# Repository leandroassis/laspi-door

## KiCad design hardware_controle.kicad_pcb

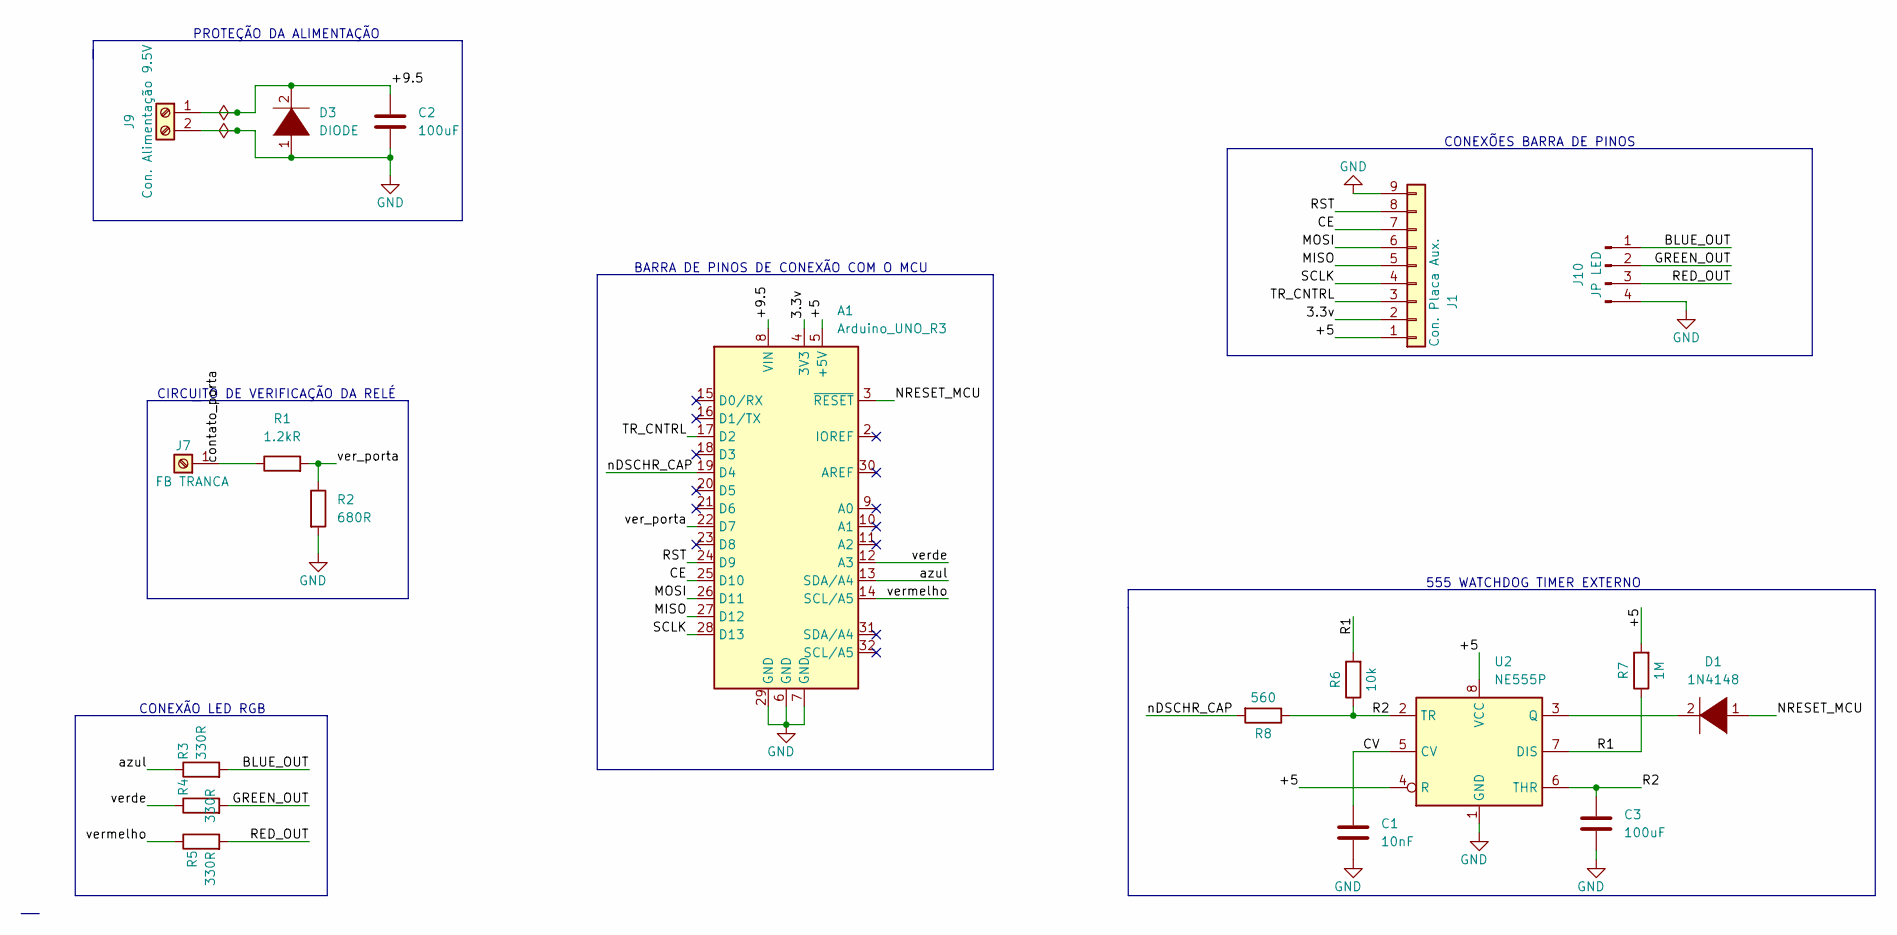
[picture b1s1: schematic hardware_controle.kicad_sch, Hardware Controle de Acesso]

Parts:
A1: Arduino_UNO_R3
C1: 10nF; C_Radial_D8.0mm_H11.5mm_P3.50mm
C2, C3: 100uF; C_Radial_D8.0mm_H11.5mm_P3.50mm
D1: 1N4148; D_DO-41_SOD81_P7.62mm_Horizontal
D3: DIODE; D_DO-41_SOD81_P7.62mm_Horizontal
J1: Con. Placa Aux.; PinHeader_1x09_P2.54mm_Vertical
J7: FB TRANCA; TerminalBlock_RND_205-00012_1x02_P5.00mm_Horizontal
J9: Con. Alimentação 9.5V; TerminalBlock_RND_205-00012_1x02_P5.00mm_Horizontal
J10: JP LED; PinHeader_1x04_P2.54mm_Vertical
R1: 1.2kR; R_Axial_DIN0207_L6.3mm_D2.5mm_P10.16mm_Horizontal
R2: 680R; R_Axial_DIN0207_L6.3mm_D2.5mm_P10.16mm_Horizontal
R3, R4, R5: 330R; R_Axial_DIN0207_L6.3mm_D2.5mm_P10.16mm_Horizontal
R6: 10k; R_Axial_DIN0207_L6.3mm_D2.5mm_P10.16mm_Horizontal
R7: 1M; R_Axial_DIN0207_L6.3mm_D2.5mm_P10.16mm_Horizontal
R8: 560; R_Axial_DIN0207_L6.3mm_D2.5mm_P10.16mm_Horizontal
U2: NE555P; DIP-8_W7.62mm

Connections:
/3.3v: A1.4 (3V3), J1.2
/+5: A1.5 (+5V), J1.1, R7.2, U2.4 (R), U2.8 (VCC)
/+9.5: A1.8 (VIN), C2.1, D3.2 (A), J9.1
/BLUE_OUT: J10.1, R3.2
/CE: A1.25 (D10), J1.7
/CV: C1.1, U2.5 (CV)
/GREEN_OUT: J10.2, R4.2
/MISO: A1.27 (D12), J1.5
/MOSI: A1.26 (D11), J1.6
/NRESET_MCU: A1.3 (~RESET), D1.1 (K)
/R1: R6.2, R7.1, U2.7 (DIS)
/R2: C3.1, R6.1, R8.1, U2.2 (TR), U2.6 (THR)
/RED_OUT: J10.3, R5.2
/RST: A1.24 (D9), J1.8
/SCLK: A1.28 (D13), J1.4
/TR_CNTRL: A1.17 (D2), J1.3
/azul: A1.13 (SDA/A4), R3.1
/nDSCHR_CAP: A1.19 (D4), R8.2
/ver_porta: A1.22 (D7), R1.2, R2.1
/verde: A1.12 (A3), R4.1
/vermelho: A1.14 (SCL/A5), R5.1
GND: A1.6 (GND), A1.7 (GND), A1.29 (GND), C1.2, C2.2, C3.2, D3.1 (K), J1.9, J9.2, J10.4, R2.2, U2.1 (GND)
unnamed: D1.2 (A), U2.3 (Q)
unnamed: J7.1, R1.1

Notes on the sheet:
CIRCUITO DE VERIFICAÇÃO DA RELÉ
555 WATCHDOG TIMER EXTERNO
BARRA DE PINOS DE CONEXÃO COM O MCU
CONEXÕES BARRA DE PINOS
CONEXÃO LED RGB
PROTEÇÃO DA ALIMENTAÇÃO

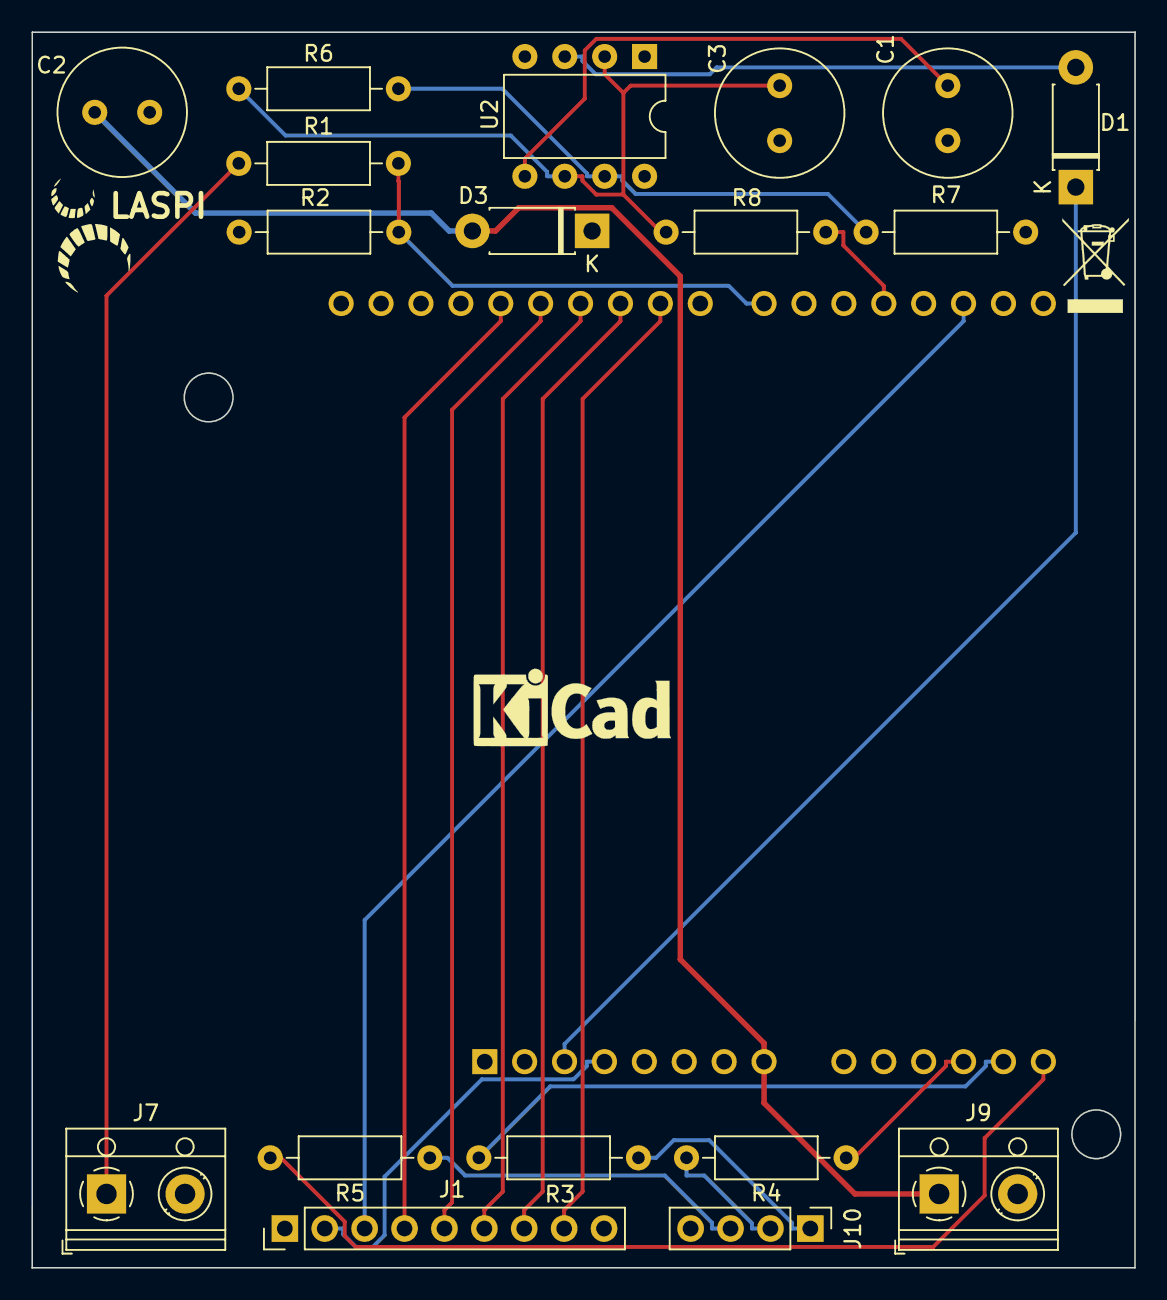
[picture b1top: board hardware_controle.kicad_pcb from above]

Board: 4 copper layers, 70.2 x 78.7 mm, 21 parts (1 on the bottom side), 24 nets.

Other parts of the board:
REFe: KiCad-Logo_5mm_SilkScreen
logolaspi: LOGO; laspi

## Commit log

2022-06-06 Fazendo adição de cadastro e remoção via ethernet
2022-06-07 Atualização usando websockets
2022-06-07 web socket falhou
2022-06-07 versão com ethernet que cabe no uno
2022-06-08 nada resolvido kk
2022-06-10 porta funcionando com interface ethernet
2022-06-22 funcionando mas sem interface no cerberys
2022-06-28 adição da descrição textual e inicio do código do cerberus
2022-06-29 Recebimento das informações
2022-07-05 Eh, ja é alguma coisa kkkkk
2022-09-30 checkpoint
2023-01-04 remoção de arquivos ultrapassados
2023-01-04 redeclarações e correções básicas
2023-01-04 schema refeito: pwr+pinout+tranca+ver. relé
2023-01-04 refatorado: falta adicionar logica de comun
2023-01-06 comunicação com servidor estabelecida
2023-01-06 correções da escrita na EEPROM
2023-01-09 iniciando server
2023-01-09 removendo arquivos inuteis
2023-01-09 portal de login com carcaça
2023-01-09 codigo rotas web funcionadno
